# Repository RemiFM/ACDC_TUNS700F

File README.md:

# 700W 28V AC-DC Module

PCB carrier board for the Cosel TUNS700F28 AC/DC converter with 28V 25A output. The board can also be used for the TUNS700F12 and TUNS700F48 modules by swapping certain components.
The board is desgined using KiCAD 8 and contains all line filtering and safety protections as recommended in the manufacturer design guide.

> [!CAUTION]
> The power converter operates at AC voltages of 230VAC and delivers up to 700W of power. Improper handling can result in serious injury, electric shock, or fire.

## Ordering Components
A [bill of materials (BOM)](BOM.csv) is available for download. The BOM contains Digi-Key part numbers, and is formatted in a way that can be uploaded to the Digi-Key website for effortless ordering.

## Assembly
For assembly, please make use of the provided [schematic](schematic.pdf), available in pdf format.

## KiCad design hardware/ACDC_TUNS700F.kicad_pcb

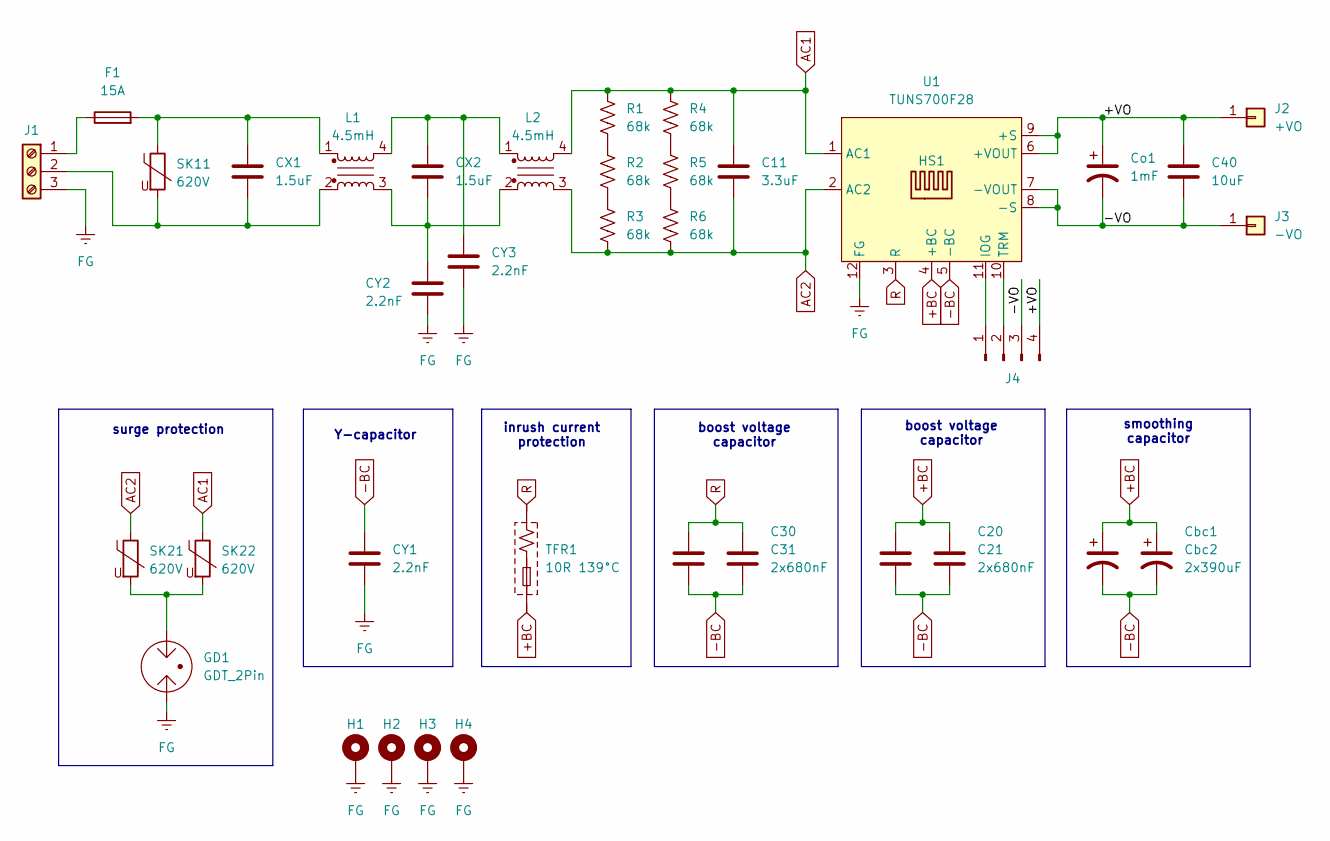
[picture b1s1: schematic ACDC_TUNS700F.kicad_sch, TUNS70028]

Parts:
C11: 3.3uF; CAP-ECQ-UAAF335K; Digi-Key P123489-ND
C20, C30: 680nF; C_Rect_L18.0mm_W8.0mm_P15.00mm_FKS3_FKP3; Digi-Key P14204-ND
C21, C31: 2x680nF; C_Rect_L18.0mm_W8.0mm_P15.00mm_FKS3_FKP3; Digi-Key P14204-ND
C40: 10uF; C_1206_3216Metric_Pad1.33x1.80mm_HandSolder; Digi-Key 445-C3216X7R1H106K160AECT-ND
CX1, CX2: 1.5uF; CAP-ECQ-UAAF155K; Digi-Key P15515-ND
CY1, CY2, CY3: 2.2nF; C_Disc_D9.0mm_W5.0mm_P10.00mm; Digi-Key 445-174537-ND
Cbc1, Cbc2: 2x390uF; CP_Radial_D30.0mm_P10.00mm_SnapIn; Digi-Key 493-7913-ND
Co1: 1mF; CP_Radial_D16.0mm_P7.50mm; Digi-Key 565-2007-ND
F1: 15A; Fuseholder_Clip-5x20mm_Littelfuse_100_Inline_P20.50x4.60mm_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; Digi-Key F3251-ND + 2 * F4225-ND
GD1: GDT_2Pin; GDT_2093-300-SM-RPLF; Digi-Key 2093-300-SM-RPLFCT-ND
H1, H2, H3, H4: MountingHole_Pad; MountingHole_2.7mm_M2.5_Pad
HS1: ATS1490-ND; Digi-Key ATS1490-ND
J1: Screw_Terminal_01x03; terminal_NC6-P108-03; Digi-Key A98496-ND
J2: +VO; Wuerth_REDCUBE-THR_WP-THRSH_74651194_THR; Digi-Key 732-74651194RCT-ND
J3: -VO; Wuerth_REDCUBE-THR_WP-THRSH_74651194_THR; Digi-Key 732-74651194RCT-ND
J4: Conn_01x04_Pin; PinHeader_1x04_P2.54mm_Vertical
L1, L2: 4.5mH; CMC_PH9455.405NL; Digi-Key 553-3962-ND
R1, R2, R3, R4, R5, R6: 68k; R_1206_3216Metric_Pad1.30x1.75mm_HandSolder; Digi-Key 311-68KERCT-ND
SK11, SK21, SK22: 620V; RV_Disc_D15,5mm_W7,1mm_P7,5mm; Digi-Key 495-5945-ND
TFR1: 10R 139°C; TFR_DFP10112; Digi-Key 285-1901-ND
U1: TUNS700F28; Digi-Key 1776-1798-ND

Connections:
+BC: C20.1, C21.1, Cbc1.1, Cbc2.1, TFR1.2, U1.4 (+BC)
-BC: C20.2, C21.2, C30.2, C31.2, CY1.1, Cbc1.2, Cbc2.2, U1.5 (-BC)
/+VO: C40.1, Co1.1, J2.1, J4.4, U1.6 (+VOUT), U1.9 (+S)
/-VO: C40.2, Co1.2, J3.1, J4.3, U1.7 (-VOUT), U1.8 (-S)
AC1: C11.1, L2.4, R1.1, R4.1, SK22.1, U1.1 (AC1)
AC2: C11.2, L2.3, R3.2, R6.2, SK21.1, U1.2 (AC2)
FG: CY1.2, CY2.2, CY3.2, GD1.1, H1.1, H2.1, H3.1, H4.1, J1.3, U1.12 (FG)
unnamed: CX1.1, F1.2, L1.1, SK11.1
unnamed: CX2.1, CY3.1, L1.4, L2.1
unnamed: CX2.2, CY2.1, L1.3, L2.2
unnamed: GD1.3, SK21.2, SK22.2
unnamed: F1.1, J1.1
unnamed: CX1.2, J1.2, L1.2, SK11.2
unnamed: J4.1, U1.11 (IOG)
unnamed: J4.2, U1.10 (TRM)
unnamed: R1.2, R2.1
unnamed: R2.2, R3.1
unnamed: R4.2, R5.1
unnamed: R5.2, R6.1
R: C30.1, C31.1, TFR1.1, U1.3 (R)

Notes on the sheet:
Y-capacitor
surge protection
boost voltage capacitor
smoothing capacitor
inrush current protection

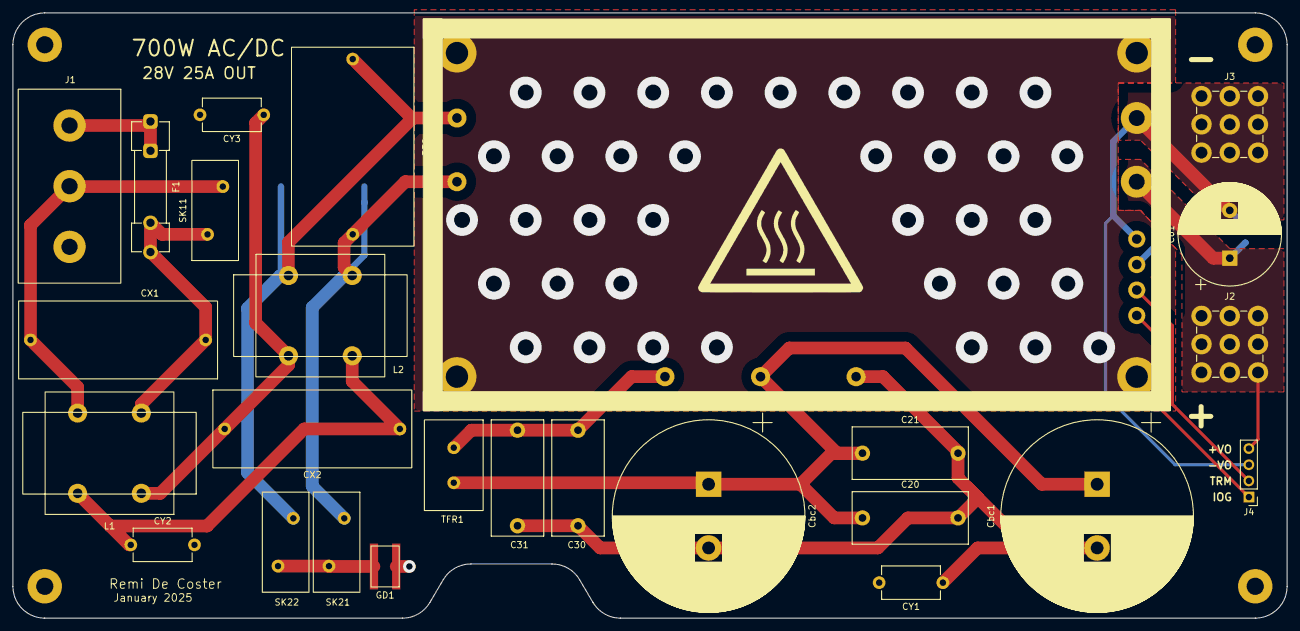
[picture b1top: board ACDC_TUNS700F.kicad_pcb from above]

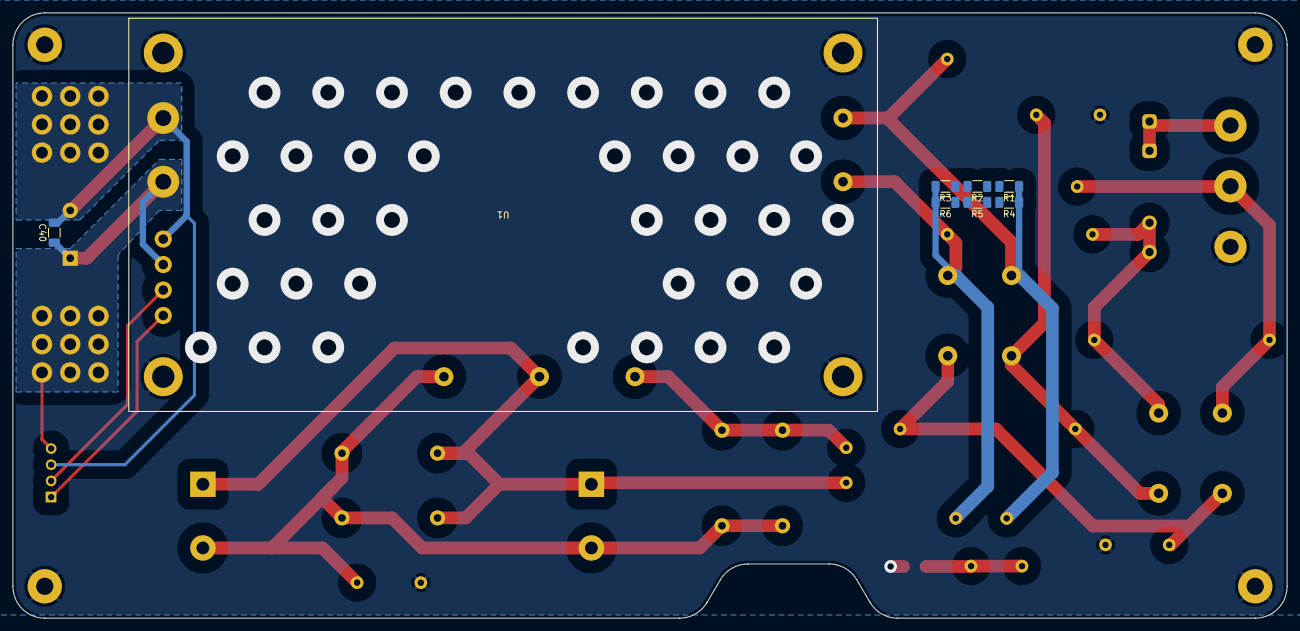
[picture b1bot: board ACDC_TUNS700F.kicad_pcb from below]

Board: 2 copper layers, 200.0 x 95.0 mm, 37 parts (8 on the bottom side), 20 nets.

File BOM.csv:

"Reference","Value","Qty","Digi-Key"
"C11","3.3uF","1","P123489-ND"
"C20,C30","680nF","2","P14204-ND"
"C21,C31","2x680nF","2","P14204-ND"
"C40","10uF","1","445-C3216X7R1H106K160AECT-ND"
"Cbc1,Cbc2","2x390uF","2","493-7913-ND"
"Co1","1mF","1","565-2007-ND"
"CX1,CX2","1.5uF","2","P15515-ND"
"CY1,CY2,CY3","2.2nF","3","445-174537-ND"
"F1","15A","1","F3251-ND + 2 * F4225-ND"
"GD1","GDT_2Pin","1","2093-300-SM-RPLFCT-ND"
"HS1","ATS1490-ND","1","ATS1490-ND"
"J1","Screw_Terminal_01x03","1","A98496-ND"
"J2","+VO","1","732-74651194RCT-ND"
"J3","-VO","1","732-74651194RCT-ND"
"J4","Conn_01x04_Pin","1",""
"L1,L2","4.5mH","2","553-3962-ND"
"R1,R2,R3,R4,R5,R6","68k","6","311-68KERCT-ND"
"SK11,SK21,SK22","620V","3","495-5945-ND"
"TFR1","10R 139°C","1","285-1901-ND"
"U1","TUNS700F28","1","1776-1798-ND"

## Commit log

2025-01-03 footprint creation
2025-01-03 input ac filter
2025-01-07 reference schematic complete
2025-01-11 board layout updates
2025-01-11 datasheets & media
2025-01-11 PCB renders
2025-01-11 Bill of materials
2025-01-11 media uploads
2025-01-11 silkscreen details
